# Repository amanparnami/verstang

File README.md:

verstang
========

Verstang is a compound name made from "vers", meaning versatile, and tang, that stands for tangibles. Tangibles could change id, behavior or feedback based on context.

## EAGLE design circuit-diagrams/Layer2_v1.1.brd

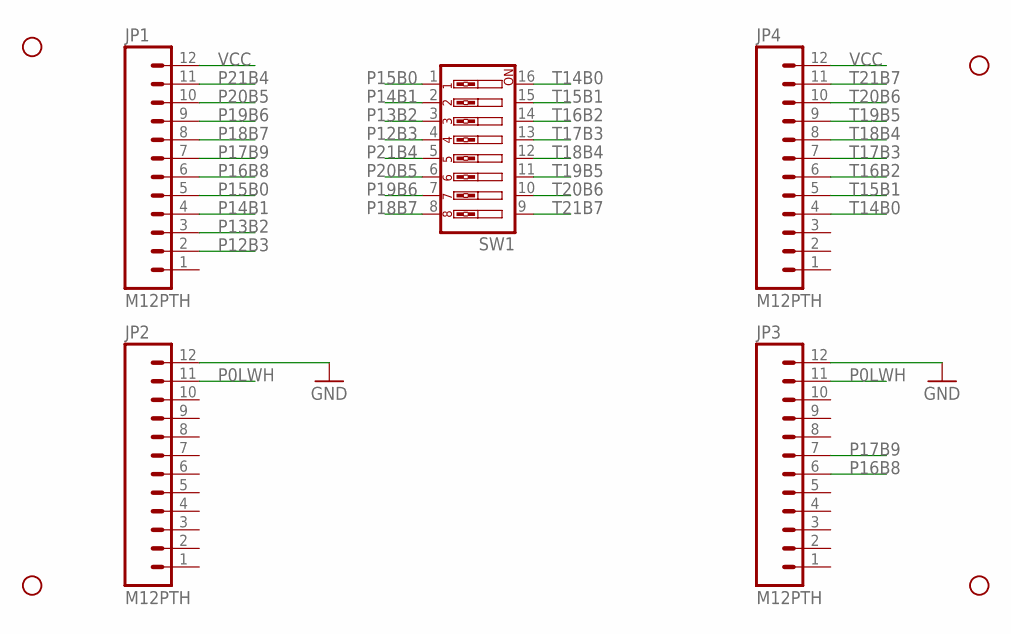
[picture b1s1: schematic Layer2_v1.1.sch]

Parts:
JP1, JP2, JP3, JP4: M12PTH; 1X12
JP5, JP6, JP7, JP8: STAND-OFF
SW1: SW_DIP-8; DIPSWITCH-08

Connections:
GND: JP2.12, JP3.12
P0LWH: JP2.11, JP3.11
P12B3: JP1.2, SW1.4
P13B2: JP1.3, SW1.3
P14B1: JP1.4, SW1.2
P15B0: JP1.5, SW1.1
P16B8: JP1.6, JP3.6
P17B9: JP1.7, JP3.7
P18B7: JP1.8, SW1.8
P19B6: JP1.9, SW1.7
P20B5: JP1.10, SW1.6
P21B4: JP1.11, SW1.5
T14B0: JP4.4, SW1.16
T15B1: JP4.5, SW1.15
T16B2: JP4.6, SW1.14
T17B3: JP4.7, SW1.13
T18B4: JP4.8, SW1.12
T19B5: JP4.9, SW1.11
T20B6: JP4.10, SW1.10
T21B7: JP4.11, SW1.9
VCC: JP1.12, JP4.12

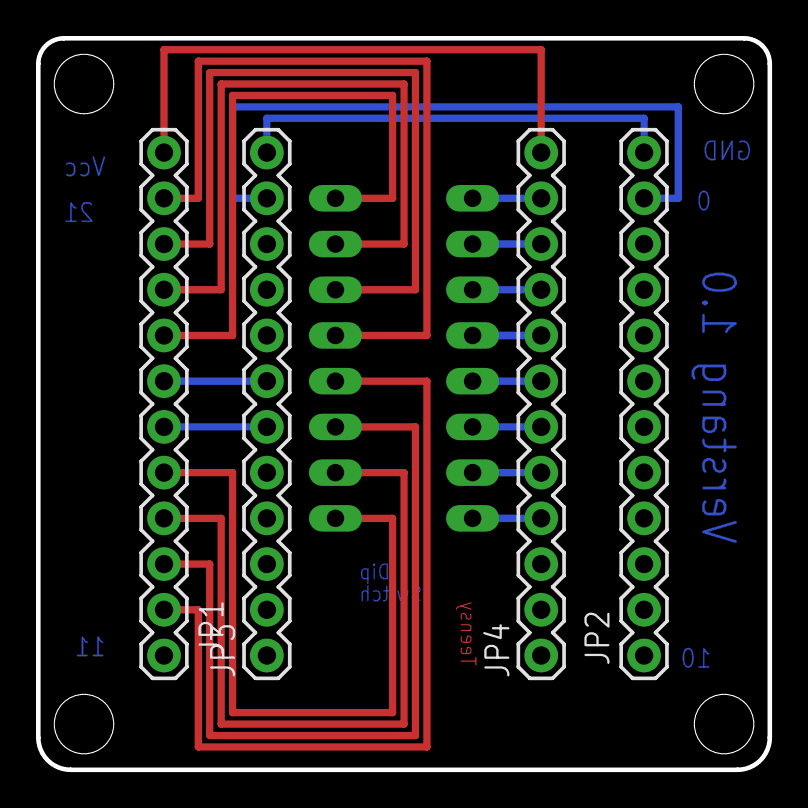
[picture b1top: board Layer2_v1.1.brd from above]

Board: 2 copper layers, 40.6 x 40.6 mm, 9 parts (1 on the bottom side), 21 nets.

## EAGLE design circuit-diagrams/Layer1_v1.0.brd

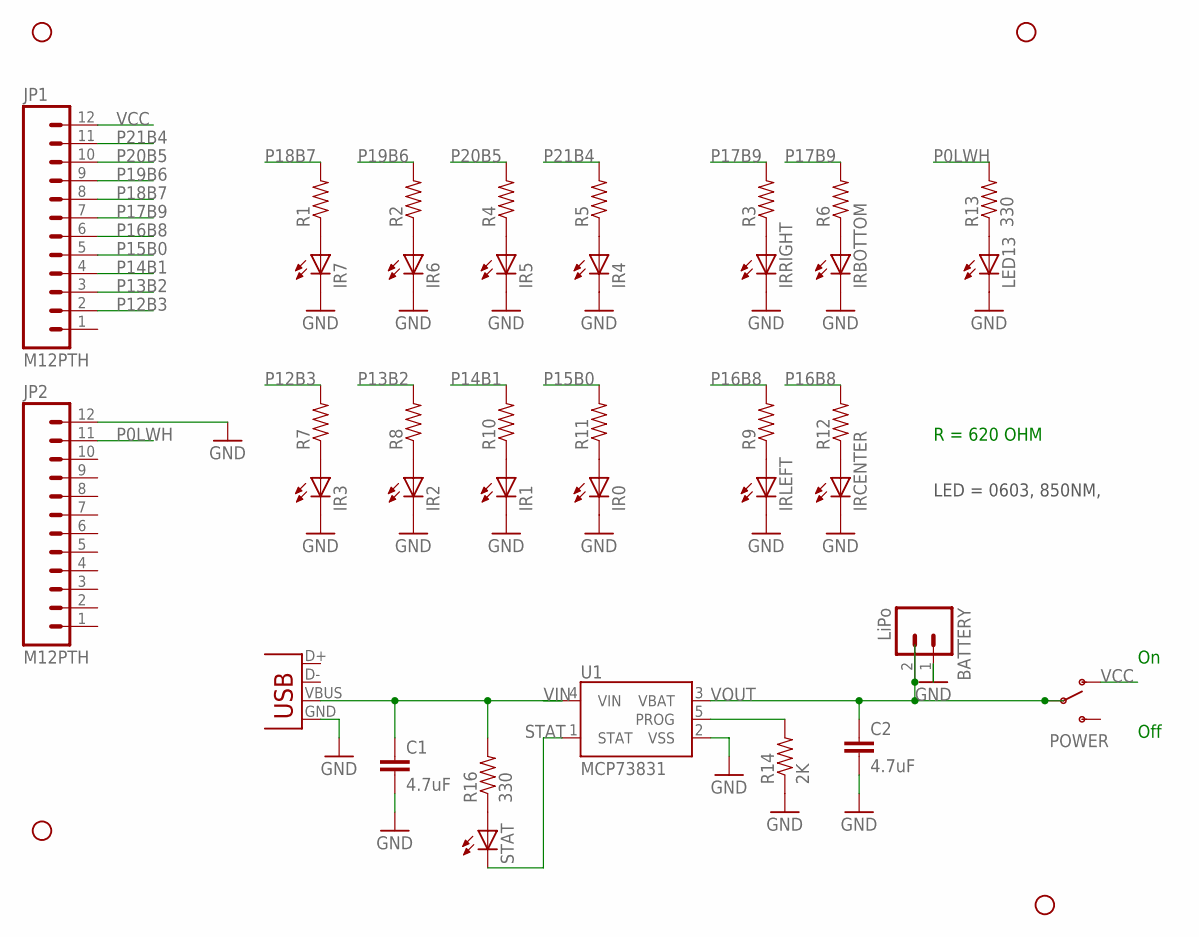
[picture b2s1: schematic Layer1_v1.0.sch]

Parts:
BATTERY: LiPo; JST-2-SMD
C1, C2: 4.7uF; 0603-CAP
IR0, IR1, IR2, IR3, IR4, IR5, IR6, IR7: LEDCHIPLED_0603; CHIPLED_0603
IRBOTTOM: LEDCHIPLED_0603; CHIPLED_0603
IRCENTER: LEDCHIPLED_0603; CHIPLED_0603
IRLEFT: LEDCHIPLED_0603; CHIPLED_0603
IRRIGHT: LEDCHIPLED_0603; CHIPLED_0603
JP1, JP2: M12PTH; 1X12
JP4, JP5, JP6, JP7: STAND-OFF
LED13: LEDCHIPLED_0603; CHIPLED_0603
POWER: SWITCH-SPDTPTH; SWITCH-SPDT
R1, R2, R3, R4, R5, R6, R7, R8, R9, R10, R11, R12: RESISTOR0603-RES; 0603-RES
R13, R16: 330; 0603-RES
R14: 2K; 0603-RES
STAT: LEDCHIPLED_0603; CHIPLED_0603
U1: MCP73831; SOT23-5
X1: USBSMD; USB-MINIB

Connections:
GND: BATTERY.1 (2), C1.2, C2.2, IR0.C, IR1.C, IR2.C, IR3.C, IR4.C, IR5.C, IR6.C, IR7.C, IRBOTTOM.C, IRCENTER.C, IRLEFT.C, IRRIGHT.C, JP2.12, LED13.C, R14.1, U1.2 (VSS), X1.GND
unnamed: LED13.A, R13.1
unnamed: IR3.A, R7.1
unnamed: IRRIGHT.A, R3.1
unnamed: IR5.A, R4.1
unnamed: IR4.A, R5.1
unnamed: IRBOTTOM.A, R6.1
unnamed: IR6.A, R2.1
unnamed: IR2.A, R8.1
unnamed: IRLEFT.A, R9.1
unnamed: IR1.A, R10.1
unnamed: IR0.A, R11.1
unnamed: IRCENTER.A, R12.1
unnamed: IR7.A, R1.1
unnamed: R16.1, STAT.A
P0LWH: JP2.11, R13.2
P12B3: JP1.2, R7.2
P13B2: JP1.3, R8.2
P14B1: JP1.4, R10.2
P15B0: JP1.5, R11.2
P16B8: JP1.6, R9.2, R12.2
P17B9: JP1.7, R3.2, R6.2
P18B7: JP1.8, R1.2
P19B6: JP1.9, R2.2
P20B5: JP1.10, R4.2
P21B4: JP1.11, R5.2
PROG: R14.2, U1.5 (PROG)
STAT: STAT.C, U1.1 (STAT)
VCC: JP1.12, POWER.1 (O)
VIN: C1.1, R16.2, U1.4 (VIN), X1.VBUS
VOUT: BATTERY.2 (1), C2.1, POWER.2, U1.3 (VBAT)

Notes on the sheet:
R = 620 OHM
LED = 0603, 850NM,
Off

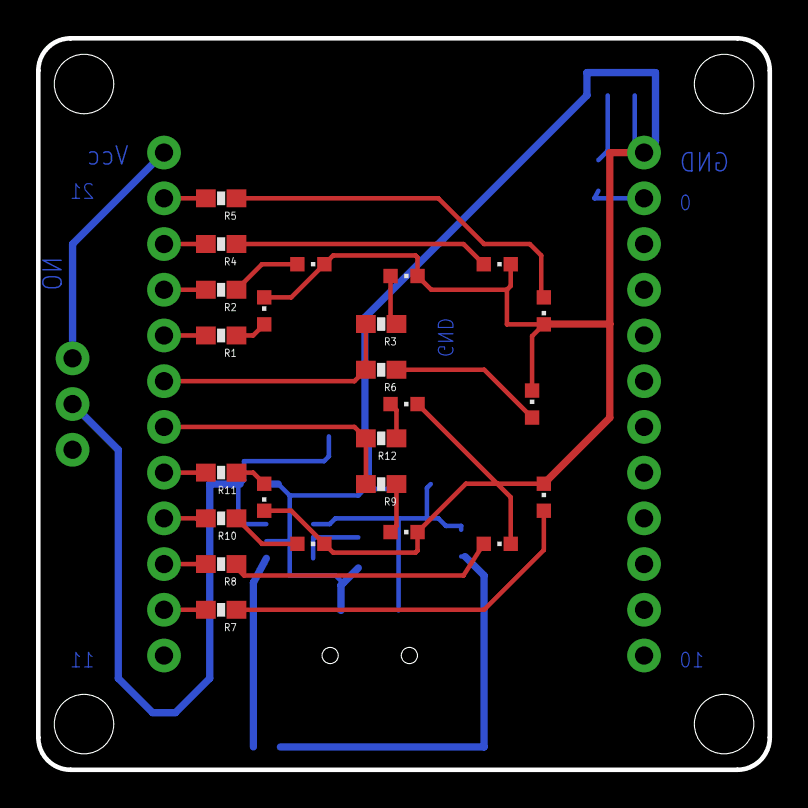
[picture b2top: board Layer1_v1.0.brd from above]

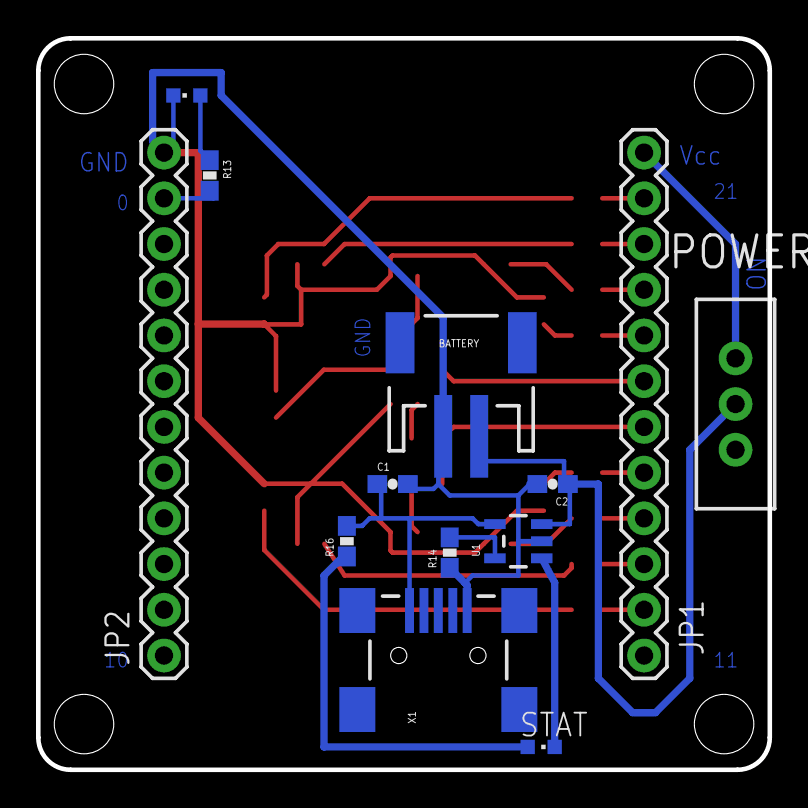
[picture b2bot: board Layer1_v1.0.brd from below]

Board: 2 copper layers, 40.6 x 40.6 mm, 41 parts (13 on the bottom side), 31 nets.

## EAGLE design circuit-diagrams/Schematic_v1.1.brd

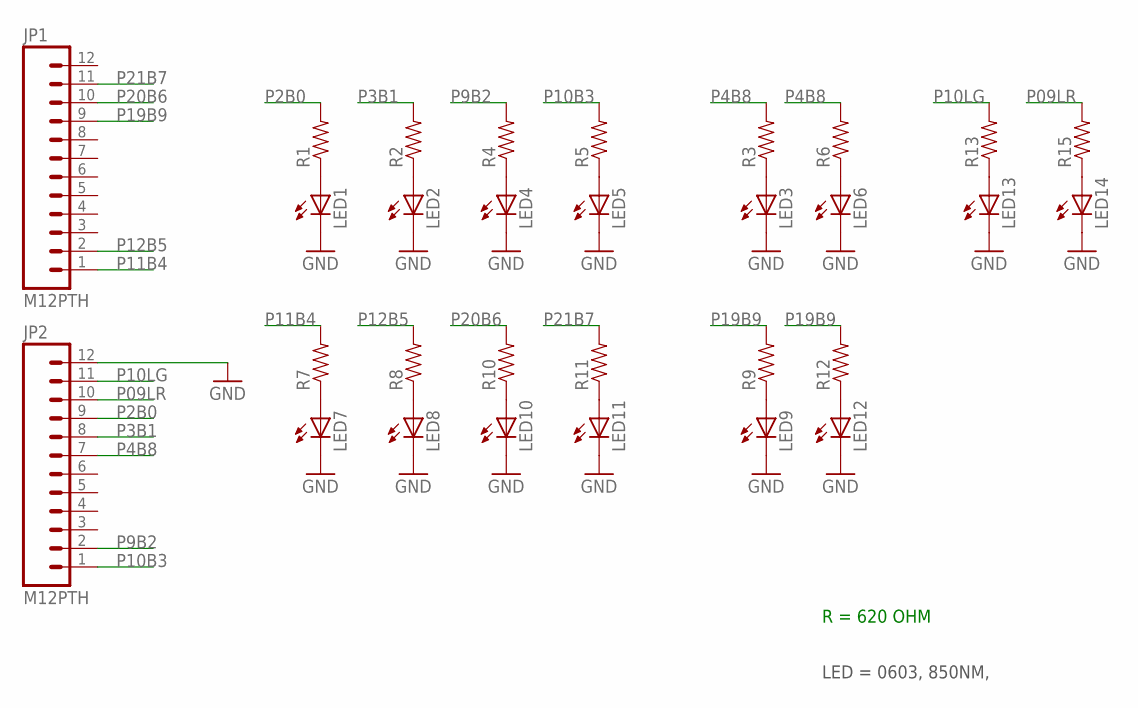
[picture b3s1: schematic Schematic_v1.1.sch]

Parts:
JP1, JP2: M12PTH; 1X12
LED1, LED2, LED3, LED4, LED5, LED6, LED7, LED8, LED9, LED10, LED11, LED12, LED13, LED14: LEDCHIPLED_0603; CHIPLED_0603
R1, R2, R3, R4, R5, R6, R7, R8, R9, R10, R11, R12, R13, R15: RESISTOR0603-RES; 0603-RES

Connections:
GND: JP2.12, LED1.C, LED2.C, LED3.C, LED4.C, LED5.C, LED6.C, LED7.C, LED8.C, LED9.C, LED10.C, LED11.C, LED12.C, LED13.C, LED14.C
unnamed: LED13.A, R13.1
unnamed: LED7.A, R7.1
unnamed: LED3.A, R3.1
unnamed: LED4.A, R4.1
unnamed: LED5.A, R5.1
unnamed: LED6.A, R6.1
unnamed: LED2.A, R2.1
unnamed: LED8.A, R8.1
unnamed: LED9.A, R9.1
unnamed: LED10.A, R10.1
unnamed: LED11.A, R11.1
unnamed: LED12.A, R12.1
unnamed: LED1.A, R1.1
unnamed: LED14.A, R15.1
P2B0: JP2.9, R1.2
P3B1: JP2.8, R2.2
P4B8: JP2.7, R3.2, R6.2
P9B2: JP2.2, R4.2
P09LR: JP2.10, R15.2
P10B3: JP2.1, R5.2
P10LG: JP2.11, R13.2
P11B4: JP1.1, R7.2
P12B5: JP1.2, R8.2
P19B9: JP1.9, R9.2, R12.2
P20B6: JP1.10, R10.2
P21B7: JP1.11, R11.2

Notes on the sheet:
R = 620 OHM
LED = 0603, 850NM,

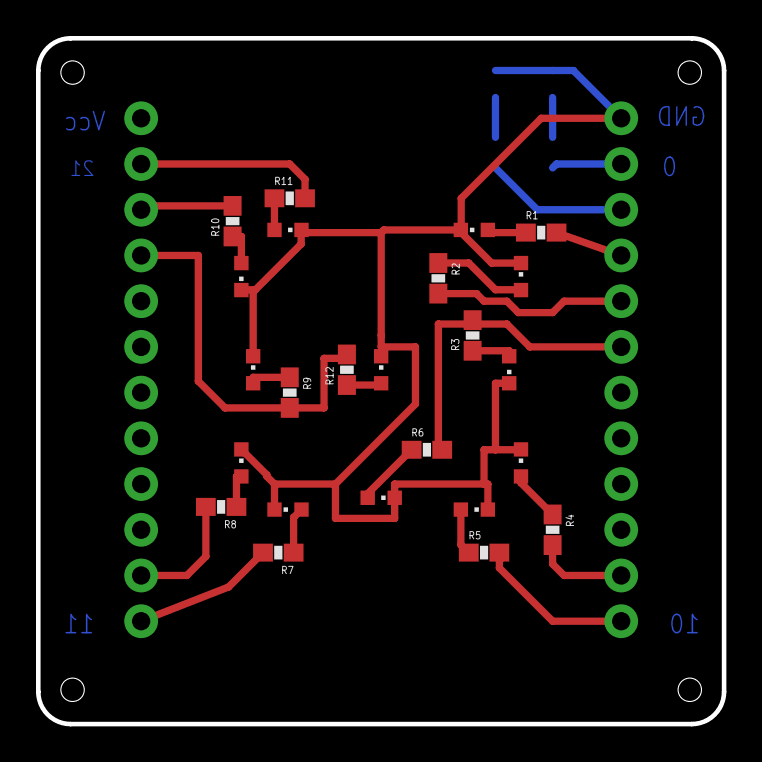
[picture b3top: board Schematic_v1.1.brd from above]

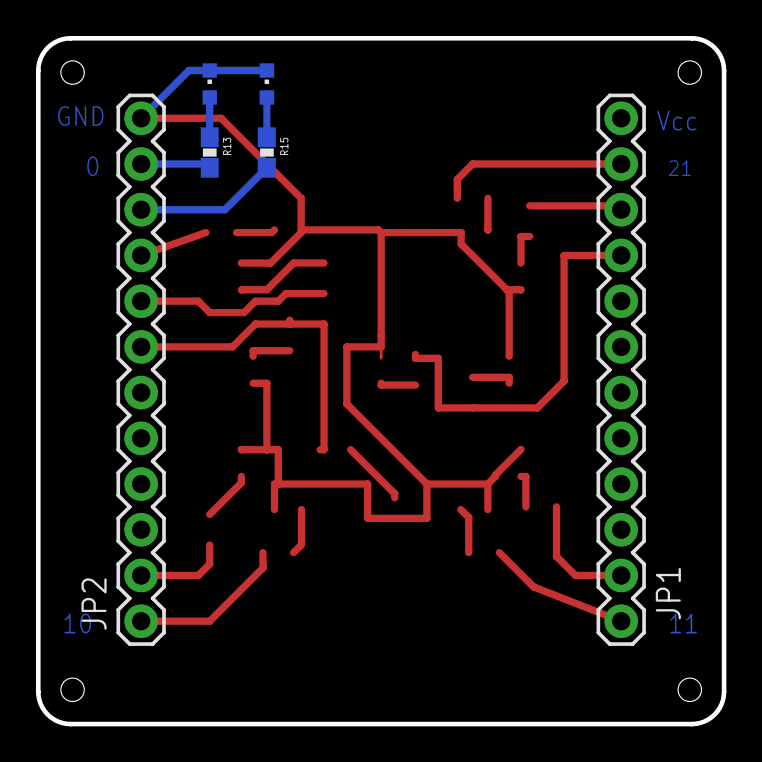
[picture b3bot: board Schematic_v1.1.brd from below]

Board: 2 copper layers, 38.1 x 38.1 mm, 30 parts (6 on the bottom side), 27 nets.

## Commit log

2013-02-26 First commit; Schematic for PCB v1.0
2013-03-16 Added Eaglle files for Layer 1
    Layer contains the ir led and battery management.
2013-03-16 Committed eagle files for layer 2
    Layer 2 contains dip switch.
2013-03-16 Version 1.1 of Layer 1 schematic
2013-03-16 Added Arduino code for changing the id.
2013-03-17 Added Layer CircuitCAM, Eagle, BoardMaster files
2013-03-17 Added Layer2 CircuitCam, Eagle, BoardMaster files
2013-03-23 Renamed arduino code folder and file.
2013-03-23 Fixed mapping of pins in layer 2 in v1.1
2013-03-24 Added laser cutter design for base and related notes
2013-03-24 Consequence of upgrading Eagle to 6.4
2013-03-24 Updated base with unmodified marker layout.

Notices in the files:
parts and their libraries:
SparkFun-Passives: Licensing: CC v3.0 Share-Alike You are welcome to use this library for commercial purposes.
